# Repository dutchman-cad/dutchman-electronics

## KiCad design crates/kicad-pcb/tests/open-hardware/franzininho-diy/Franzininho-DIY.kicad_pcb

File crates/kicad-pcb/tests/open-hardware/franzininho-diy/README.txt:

Openly licensed board by others, not CC0. License: CC-BY-SA-4.0, https://creativecommons.org/licenses/by-sa/4.0/

Franzininho DIY, an open-hardware board by the Franzininho project, used here as a larger real-world test case. It is NOT CC0.

License: Creative Commons Attribution-ShareAlike 4.0 International (CC BY-SA 4.0), https://creativecommons.org/licenses/by-sa/4.0/ . The full text is in LICENSE-CC-BY-SA-4.0.txt, copied from the project. The project is certified by OSHWA (UID BR000003), and the board's own silkscreen says "CC BY-SA 4.0".
Attribution (what CC BY-SA 4.0 asks for): "Franzininho DIY" (version V2RV3 on the silkscreen) by the Franzininho project (https://www.franzininho.com.br), licensed under CC BY-SA 4.0. We changed the file only by saving it again in KiCad 9.0 (see below). ShareAlike: this file, and any adapted copy of it, stays under CC BY-SA 4.0. The license covers this board file only; the Apache-2.0 license of the rest of the repository does not apply to it, and reading the file with our code does not make our code a derivative of it.

Source: https://github.com/Franzininho/franzininho-diy-board , file "Franzininho DIY/Franzininho.kicad_pcb", commit abdb4b48d867190d6b9794280be8b85b81aa1772 (default branch on 2026-11-25; the board is also in the project's tagged releases, v2.2 and earlier).

How the file in this folder was made: the file at that commit was written by KiCad 5.1 (file version 20171130). We opened it in KiCad 9.0 (container kicad/kicad:9.0, pcbnew Python: LoadBoard, then SaveBoard) and saved it, so it is in the KiCad 9 file format (version 20241229). Nothing else was edited or removed. KiCad warned that the legacy zone fill strategy is not supported and converted the zone fill; the zone has a fill in the saved file. The project and settings files KiCad writes beside it are not included. One footprint names an external 3D model (${KIPRJMOD}/library.pretty/USB-AM-S-F-B-TH.stp); that file is not in this folder.

Privacy: the board file was scanned for paths, e-mail addresses, computer names and user names before it was committed: none. It has no title block.

Numbers, as KiCad 9.0 gives them for the file in this folder (pcbnew Python, not our reader):
- Outline (Edge.Cuts): 4 lines (width 0.15), one closed contour, no cutouts. Size on the line centers 51.0675 x 30.0300 mm (51.2175 x 30.1800 including the line width). In KiCad's page coordinates the center lines run from (122.9673, 89.9886) to (174.0349, 120.0186); Y points down.
- Thickness: 1.600 mm (general thickness; no stack-up table).
- Copper layers: 2 (top and bottom).
- Footprints: 30, 28 on the top side and 2 on the bottom. For example X1 USB-A-H, IC1 DIP-8_W7.62mm_Socket_LongPads, RESET TAC-SWITCH-PTH, four mounting-hole footprints named @HOLE0 to @HOLE3 and several logo footprints.
- Pads: 62. Tracks: 157. Vias: 0. Arc tracks: 0. Zones: 1. Nets: 15.

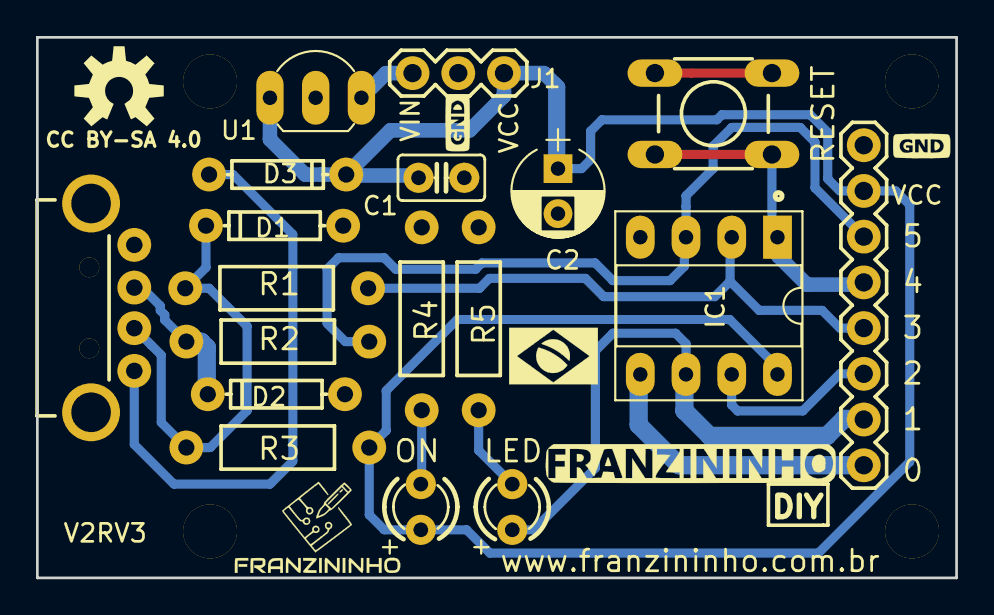
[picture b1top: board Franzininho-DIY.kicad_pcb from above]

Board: 2 copper layers, 51.1 x 30.0 mm, 23 parts (0 on the bottom side), 14 nets.

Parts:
@HOLE0, @HOLE1, @HOLE2, @HOLE3: (no value)
C1: 0.1uf; C025-025X050
C2: 10uF; CP_Radial_D5.0mm_P2.50mm
D1, D2: BZT52; DIODE-BZT52
D3: 1N4148; DIODE-1N4148
IC1: ATTINY85 - 20PU; DIP-8_W7.62mm_Socket_LongPads
J1: M03PTH; 1X03
JP3: M08; 1X08_ROUND
LED: LED3MM
LOGO1: OSHW-LOGOM; OSHW-LOGO-M
ON: LED3MM
R1, R2: 68R; AXIAL-0.4
R3: 1K5; AXIAL-0.4
R4, R5: 1K; AXIAL-0.4
RESET: TACTILE-SWITCH-PTH; TAC-SWITCH-PTH
U1: L78L05_TO92; TO-92_Inline_Wide
X1: USB-A-H

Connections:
5V: C1.1, C2.1, D3.C, IC1.8, J1.1, JP3.7, ON.A, R3.P$1, U1.1
GND: C1.2, C2.2, D1.A, D2.A, IC1.4, J1.2, JP3.8, R4.P$1, R5.P$1, RESET.3, RESET.4, U1.2, X1.GND
unnamed: D1.C, R1.P$1, R3.P$2, X1.D-
unnamed: D2.C, R2.P$1, X1.D+
unnamed: D3.A, X1.VBUS
unnamed: IC1.1, JP3.5, RESET.1, RESET.2
unnamed: IC1.2, JP3.4, R1.P$2
unnamed: IC1.3, JP3.6, R2.P$2
unnamed: IC1.5, JP3.1
unnamed: IC1.6, JP3.2, LED.A
unnamed: IC1.7, JP3.3
unnamed: J1.3, U1.3
unnamed: LED.K, R5.P$2
unnamed: ON.K, R4.P$2

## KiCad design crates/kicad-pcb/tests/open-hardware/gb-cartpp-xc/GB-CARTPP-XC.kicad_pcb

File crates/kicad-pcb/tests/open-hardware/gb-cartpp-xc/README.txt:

Openly licensed board by others, not CC0. License: CC-BY-4.0, https://creativecommons.org/licenses/by/4.0/

GB-CARTPP-XC, an open-hardware board by gekkio, used here as a larger real-world test case. It is NOT CC0.

License: Creative Commons Attribution 4.0 International (CC BY 4.0), https://creativecommons.org/licenses/by/4.0/ . The full text is in LICENSE-CC-BY-4.0.txt, copied from the project.
Attribution (what CC BY 4.0 asks for): "GB-CARTPP-XC" by gekkio (https://gekkio.fi), from the project "Game Boy -related custom hardware by gekkio", licensed under CC BY 4.0. We changed the file only by saving it again in KiCad 9.0 (see below). The creator's name and website are still in the board file (title block and silkscreen text), as the project asks.

Source: https://github.com/Gekkio/gb-hardware , folder GB-CARTPP-XC, file GB-CARTPP-XC.kicad_pcb, commit b5ade559bd988fd6c4f5941615d4d6d79dec9098 (default branch on 2026-11-25; the project has no release tags). The board's own revision is v1.2 (title block), dated 2020-10-04.

How the file in this folder was made: the file at that commit was written by KiCad 6 (file version 20221018). We opened it in KiCad 9.0 (container kicad/kicad:9.0, pcbnew Python: LoadBoard, then SaveBoard) and saved it, so it is in the KiCad 9 file format (version 20241229). Nothing else was edited or removed. The project and settings files KiCad writes beside it are not included. The board stores no 3D model files; its footprints name models from KiCad's standard library (${KISYS3DMOD}/...) and the project's own library.

Privacy: the board file was scanned for paths, e-mail addresses, computer names and user names before it was committed: none. Its title block holds only the project's public name, revision, date and the creator's website (the attribution above).

Numbers, as KiCad 9.0 gives them for the file in this folder (pcbnew Python, not our reader):
- Outline (Edge.Cuts): 8 items, four lines and four rounded corners (arcs), one closed contour, no cutouts. Size on the line centers 80.000 x 55.000 mm (80.050 x 55.050 including the 0.05 line width). In KiCad's page coordinates the center lines run from (50, 50) to (130, 105); Y points down.
- Thickness: 1.000 mm (general thickness; no stack-up table).
- Copper layers: 2 (F.Cu, B.Cu).
- Footprints: 29, all on the top side (0 on the bottom). For example U2 TQFP-44_10x10mm_P0.8mm, J3 GameBoy_Cartridge_AGS_1x32-1MP_P1.50mm_Socket_Horizontal, J1 USB_C_Receptacle_HRO_TYPE-C-31-M-12.
- Pads: 156. Tracks: 437. Vias: 144. Arc tracks: 0. Zones: 3. Nets: 46.

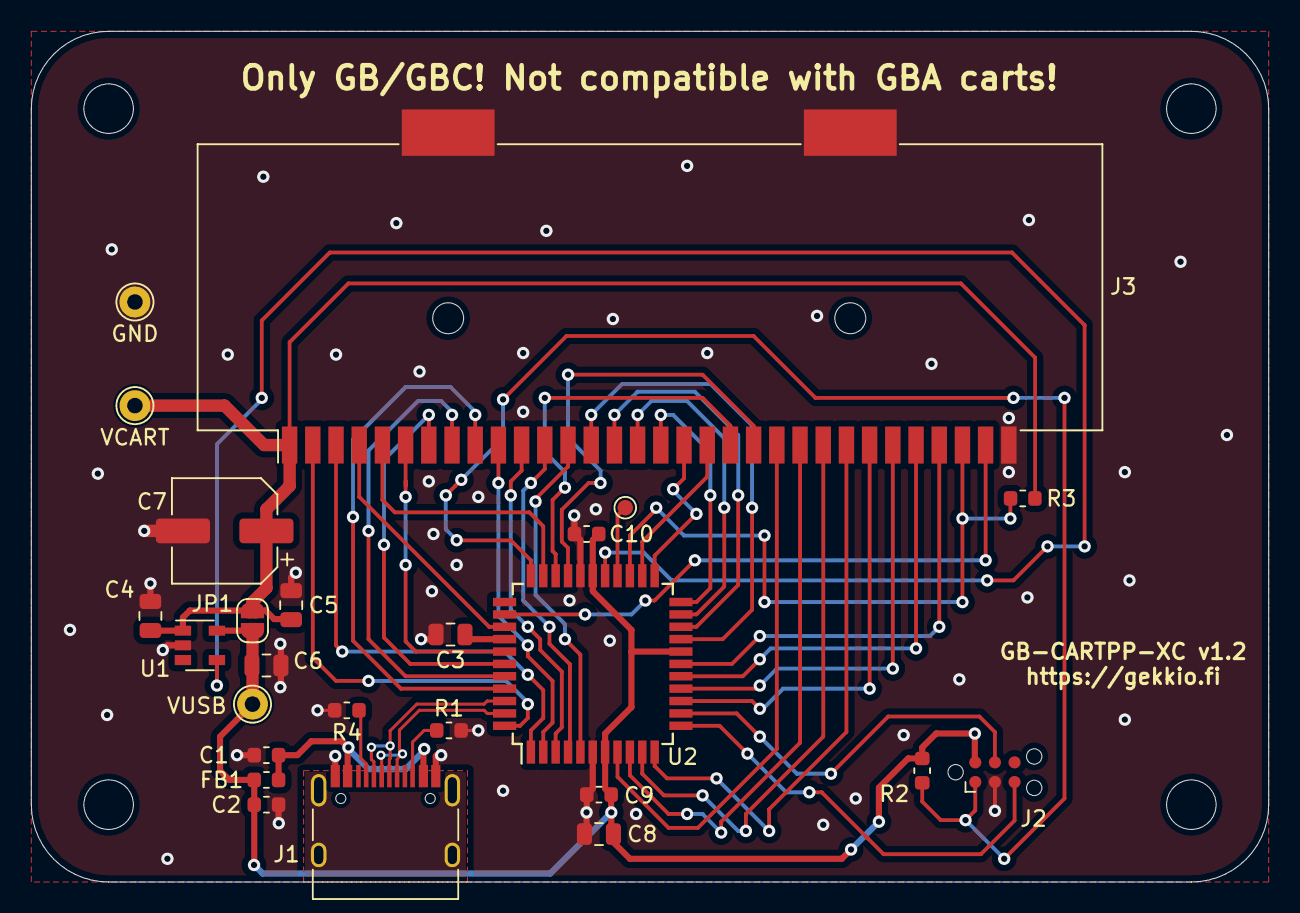
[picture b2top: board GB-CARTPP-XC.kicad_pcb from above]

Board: 2 copper layers, 80.0 x 55.0 mm, 29 parts (0 on the bottom side), 44 nets.

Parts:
C1, C2, C9, C10: 100nF; C_0603_1608Metric
C3, C8: 1uF; C_0805_2012Metric
C4, C5, C6: 4.7uF; C_0805_2012Metric
C7: 100uF; CP_Elec_6.3x5.8
FB1: MPZ1608S331; L_0603_1608Metric
H1, H2, H3, H4: DNP; MountingHole_3.2mm_M3
J1: TYPE-C-31-M-12; USB_C_Receptacle_HRO_TYPE-C-31-M-12
J2: DNP; Tag-Connect_TC2030-IDC-NL_2x03_P1.27mm_Vertical
J3: GameBoy_Cartridge_MountingPin; GameBoy_Cartridge_AGS_1x32-1MP_P1.50mm_Socket_Horizontal
JP1: BYPASS; SolderJumper-2_P1.3mm_Open_RoundedPad1.0x1.5mm
R1, R4: 5k1; R_0603_1608Metric
R2, R3: 10k; R_0603_1608Metric
TP1: VUSB; TestPoint_THTPad_D2.0mm_Drill1.0mm
TP2: RE1; TestPoint_Pad_D1.0mm
TP3: VCART; TestPoint_THTPad_D2.0mm_Drill1.0mm
TP4: GND; TestPoint_THTPad_D2.0mm_Drill1.0mm
U1: SY6288AAAC; SOT-23-5
U2: PIC18F45K50_QFP; TQFP-44_10x10mm_P0.8mm

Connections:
+5V: C2.1, C6.1, C8.1, C9.1, C10.1, FB1.2, J2.2, JP1.1, R2.1, TP1.1, U1.5, U2.7, U2.18, U2.28
/A0: J3.6, U2.38
/A1: J3.7, U2.39
/A2: J3.8, U2.40
/A3: J3.9, U2.41
/A4: J3.10, U2.2
/A5: J3.11, U2.3
/A6: J3.12, U2.4
/A7: J3.13, U2.5
/A8: J3.14, U2.19
/A9: J3.15, U2.20
/A10: J3.16, U2.21
/A11: J3.17, U2.22
/A12: J3.18, U2.23
/A13: J3.19, U2.24
/A14: J3.20, U2.31
/A15: J3.21, U2.30
/D0: J3.22, U2.8
/D1: J3.23, U2.9
/D2: J3.24, U2.10
/D3: J3.25, U2.11
/D4: J3.26, U2.14
/D5: J3.27, U2.15
/D6: J3.28, U2.16
/D7: J3.29, U2.17
/PGC: J2.5, U2.12
/PGD: J2.4, U2.13
/PHI: J3.2, U2.44
/TP_RE1: TP2.1, U2.26
/USB_N: J1.A7, J1.B7, U2.42
/USB_P: J1.A6, J1.B6, U2.43
/VPP: J2.1, R2.2, U2.33
/~CS: J3.5, U2.32
/~P31: J3.31, U2.35
/~RD: J3.4, U2.36
/~RES: J3.30, R3.2, U2.25
/~WR: J3.3, U2.1
GND: C1.2, C2.2, C3.2, C4.2, C5.2, C6.2, C7.2, C8.2, C9.2, C10.2, J1.A1, J1.A12, J1.B1, J1.B12, J2.3, J3.32, J3.MP, R1.2, R4.2, TP4.1, U1.2, U2.6, U2.29
unnamed: C1.1, FB1.1, J1.A4, J1.A9, J1.B4, J1.B9
unnamed: C3.1, U2.37
unnamed: J1.A5, R4.1
unnamed: J1.B5, R1.1
unnamed: U1.4, U2.27
VCART: C4.1, C5.1, C7.1, J3.1, JP1.2, R3.1, TP3.1, U1.1
